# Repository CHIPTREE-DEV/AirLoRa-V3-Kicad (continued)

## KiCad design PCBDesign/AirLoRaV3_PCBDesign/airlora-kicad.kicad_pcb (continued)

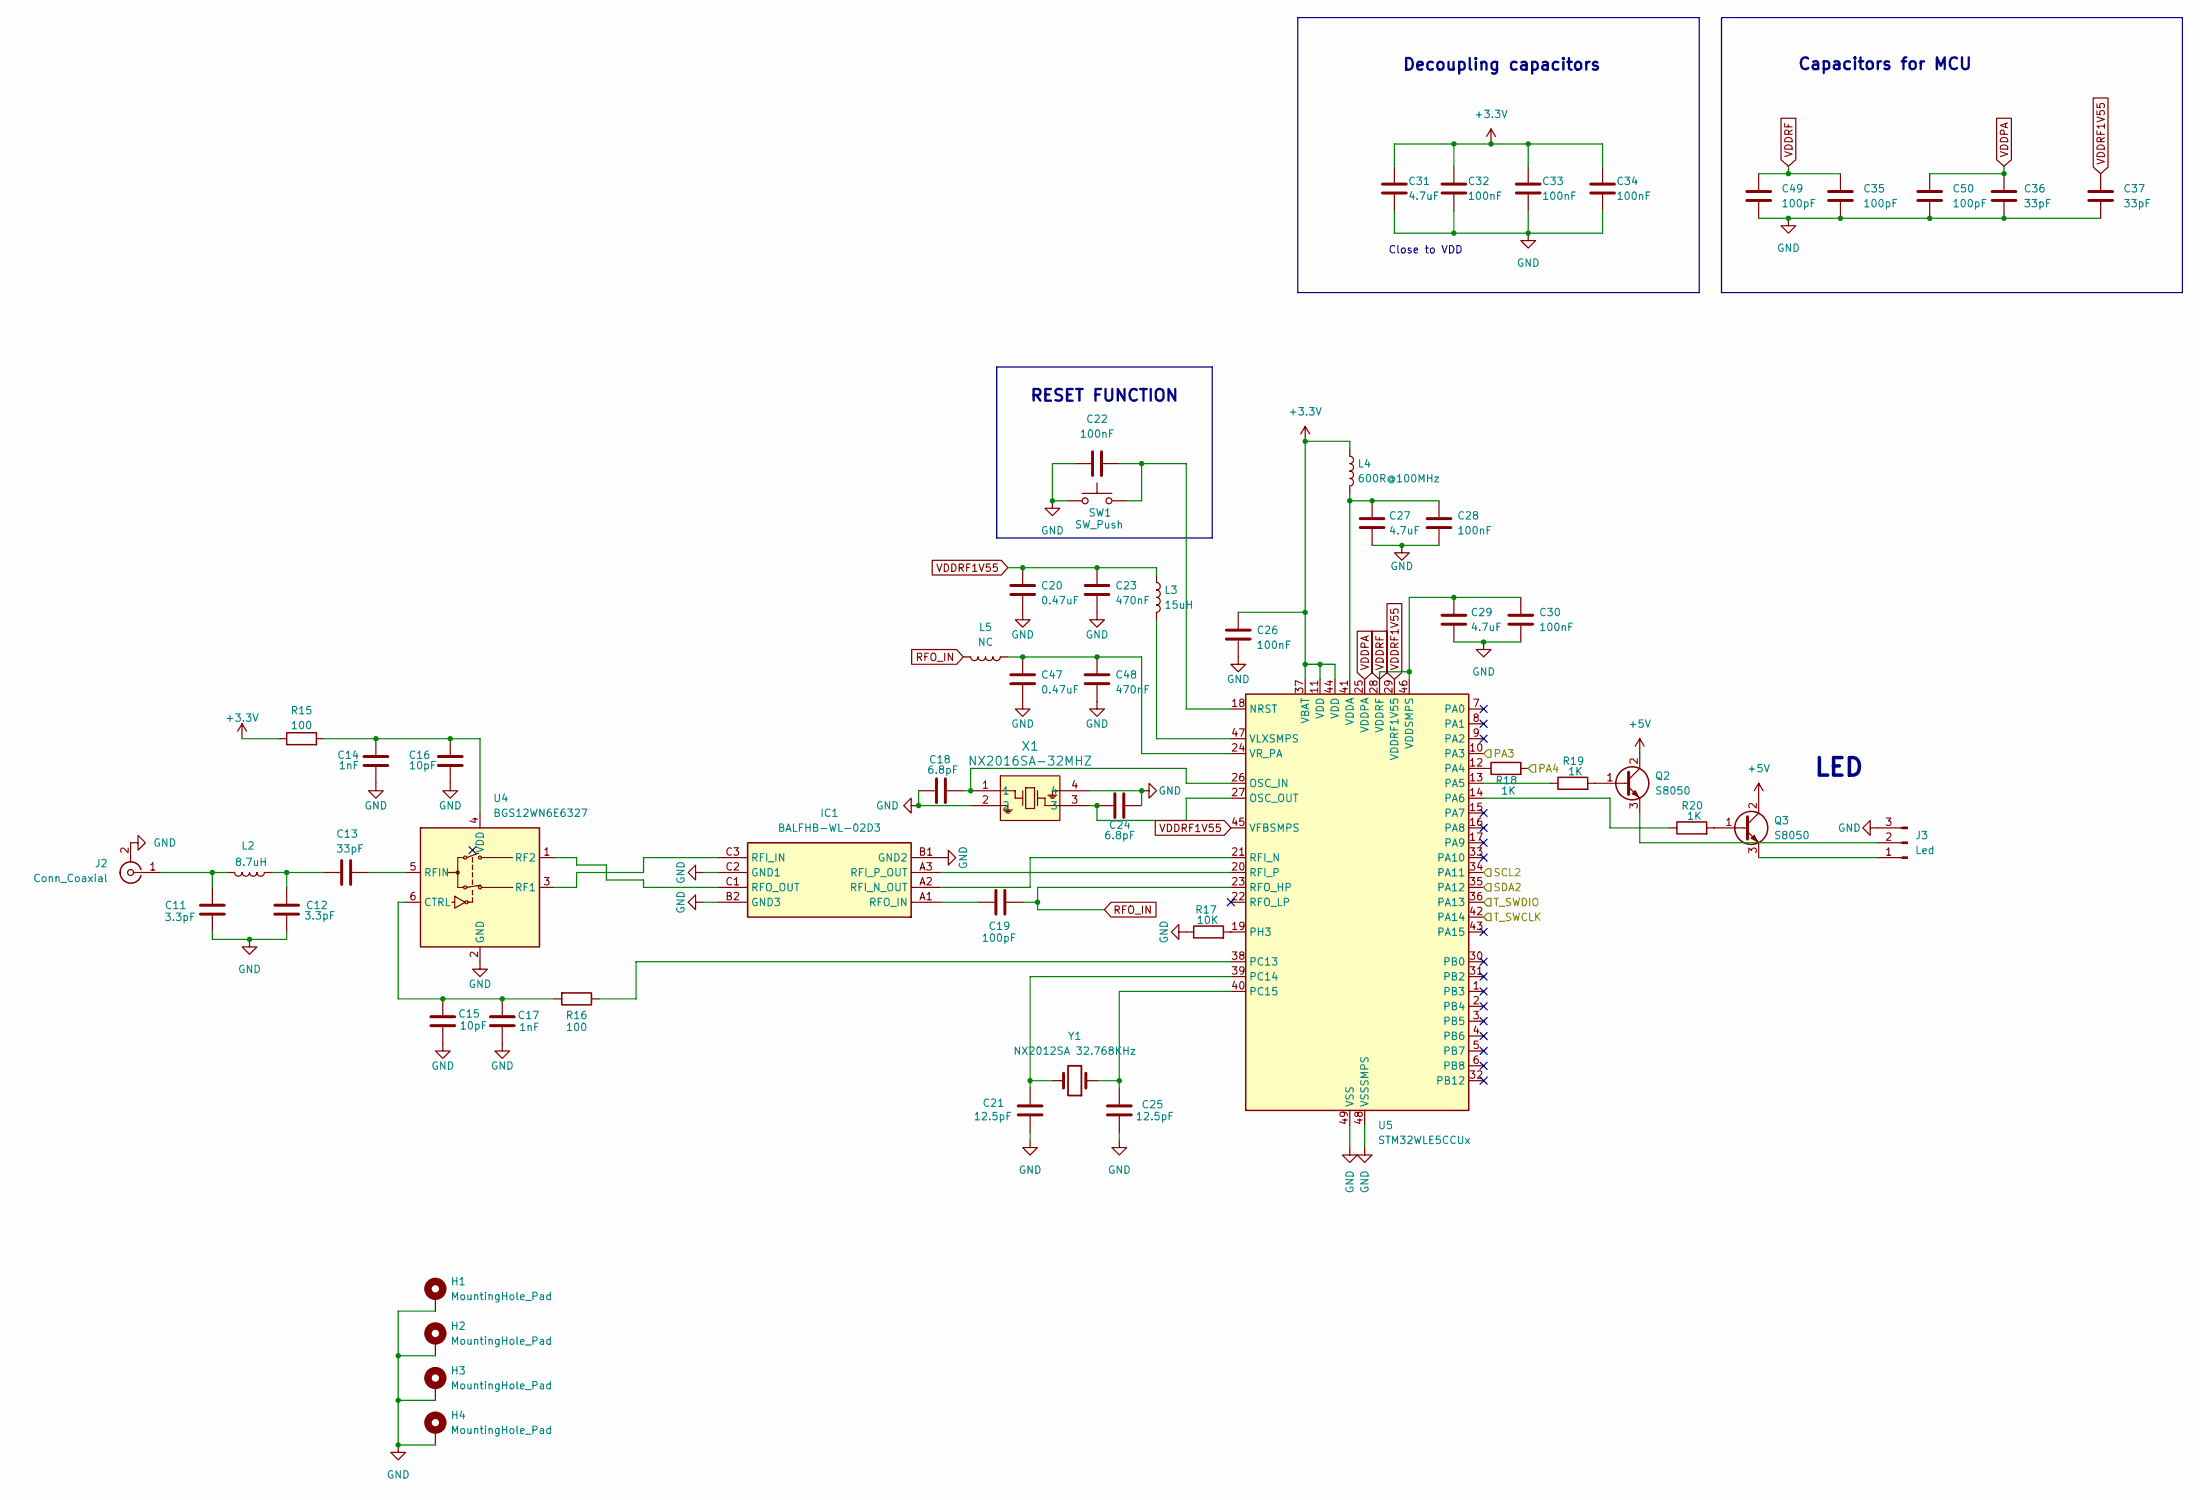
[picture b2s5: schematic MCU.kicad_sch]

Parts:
C11, C12: 3.3pF; C_0402_1005Metric_Pad0.74x0.62mm_HandSolder
C13, C36, C37: 33pF; C_0402_1005Metric_Pad0.74x0.62mm_HandSolder
C14, C17: 1nF; C_0402_1005Metric_Pad0.74x0.62mm_HandSolder
C15, C16: 10pF; C_0402_1005Metric_Pad0.74x0.62mm_HandSolder
C18, C24: 6.8pF; C_0402_1005Metric_Pad0.74x0.62mm_HandSolder
C19, C35, C49, C50: 100pF; C_0402_1005Metric_Pad0.74x0.62mm_HandSolder
C20, C47: 0.47uF; C_0402_1005Metric_Pad0.74x0.62mm_HandSolder
C21, C25: 12.5pF; C_0402_1005Metric_Pad0.74x0.62mm_HandSolder
C22, C26, C28, C30, C32, C33, C34: 100nF; C_0402_1005Metric_Pad0.74x0.62mm_HandSolder
C23, C48: 470nF; C_0402_1005Metric_Pad0.74x0.62mm_HandSolder
C27, C29, C31: 4.7uF; C_0402_1005Metric_Pad0.74x0.62mm_HandSolder
H1, H2, H3, H4: MountingHole_Pad; MountingHole_3mm_Pad_Via
IC1: BALFHB-WL-02D3; BALFHBWL05D3; Manufacturer_Part_Number BALFHB-WL-05D3; Mouser Part Number 511-BALFHB-WL-05D3
J2: Conn_Coaxial; U.FL_Molex_MCRF_73412-0110_Vertical
J3: Led; JST_XH_B3B-XH-A_1x03_P2.50mm_Vertical
L2: 8.7uH; L_0402_1005Metric_Pad0.77x0.64mm_HandSolder
L3: 15uH; L_0402_1005Metric_Pad0.77x0.64mm_HandSolder
L4: 600R@100MHz; L_0402_1005Metric_Pad0.77x0.64mm_HandSolder
L5: NC; L_0402_1005Metric_Pad0.77x0.64mm_HandSolder
Q2, Q3: S8050; SOT-23
R15, R16: 100; R_0402_1005Metric_Pad0.72x0.64mm_HandSolder
R17: 10K; R_0402_1005Metric_Pad0.72x0.64mm_HandSolder
R18, R19, R20: 1K; R_0402_1005Metric_Pad0.72x0.64mm_HandSolder
SW1: SW_Push; SW_Push_1P1T_NO_Vertical_Wuerth_434133025816
U4: BGS12WN6E6327; BGS12SN6E6327XTSA1
U5: STM32WLE5CCUx; QFN-48-1EP_7x7mm_P0.5mm_EP5.6x5.6mm
X1: NX2016SA-32MHZ; NX2016SA_NDK
Y1: NX2012SA 32.768KHz; XTAL_NX2012SA-32.768K-STD-MUB-1

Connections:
+3.3V: C26.1, C31.1, C32.1, C33.1, C34.1, L4.1, R15.1, U5.11 (VDD), U5.37 (VBAT), U5.44 (VDD); also elsewhere on the board
+5V: Q2.2 (C), Q3.2 (C); also elsewhere on the board
/AirLora V3/MCU Sub/PA8: R18.2; also elsewhere on the board
/AirLora V3/MCU Sub/SCL2: U5.34 (PA11); also elsewhere on the board
/AirLora V3/MCU Sub/SDA2: U5.35 (PA12); also elsewhere on the board
/AirLora V3/MCU/PA3: U5.10 (PA3); also elsewhere on the board
/AirLora V3/MCU/T_SWCLK: U5.42 (PA14); also elsewhere on the board
/AirLora V3/MCU/T_SWDIO: U5.36 (PA13); also elsewhere on the board
GND: C11.1, C12.1, C14.1, C15.2, C16.1, C17.2, C18.1, C20.2, C21.1, C22.1, C23.2, C24.2, C25.1, C26.2, C27.2, C28.2, C29.2, C30.2, C31.2, C32.2, C33.2, C34.2, C35.2, C36.2, C37.2, C47.2, C48.2, C49.2, C50.2, H1.1, H2.1, H3.1, H4.1, IC1.B1 (GND2), IC1.B2 (GND3), IC1.C2 (GND1), J2.2 (Ext), J3.3, R17.1, SW1.1, U4.2 (GND), U5.48 (VSSSMPS), U5.49 (VSS), X1.2, X1.4; also elsewhere on the board
unnamed: C12.2, C13.2, L2.1
unnamed: IC1.C3 (RFI_IN), U4.3 (RF1)
unnamed: IC1.A2 (RFI_N_OUT), U5.21 (RFI_N)
unnamed: IC1.A3 (RFI_P_OUT), U5.20 (RFI_P)
unnamed: C19.1, IC1.A1 (RFO_IN)
unnamed: IC1.C1 (RFO_OUT), U4.1 (RF2)
unnamed: C11.2, J2.1 (In), L2.2
unnamed: J3.1, Q3.3 (E)
unnamed: J3.2, Q2.3 (E)
unnamed: Q2.1 (B), R19.2
unnamed: Q3.1 (B), R20.2
unnamed: C15.1, C17.1, R16.2, U4.6 (CTRL)
unnamed: C13.1, U4.5 (RFIN)
unnamed: C14.2, C16.2, R15.2, U4.4 (VDD)
unnamed: C22.2, SW1.2, U5.18 (NRST)
unnamed: C18.2, U5.26 (OSC_IN), X1.1
unnamed: C24.1, U5.27 (OSC_OUT), X1.3
unnamed: R18.1, U5.12 (PA4)
unnamed: R19.1, U5.13 (PA5)
unnamed: R20.1, U5.14 (PA6)
unnamed: R16.1, U5.38 (PC13)
unnamed: C21.2, U5.39 (PC14), Y1.2
unnamed: C25.2, U5.40 (PC15), Y1.1
unnamed: R17.2, U5.19 (PH3)
unnamed: C27.1, C28.1, L4.2, U5.41 (VDDA)
unnamed: L3.2, U5.47 (VLXSMPS)
unnamed: C47.1, C48.1, L5.1, U5.24 (VR_PA)
RFO_IN: C19.2, L5.2, U5.23 (RFO_HP)
VDDPA: C36.1, C50.1, U5.25 (VDDPA)
VDDRF: C29.1, C30.1, C35.1, C49.1, U5.28 (VDDRF), U5.46 (VDDSMPS)
VDDRF1V55: C20.1, C23.1, C37.1, L3.1, U5.29 (VDDRF1V55), U5.45 (VFBSMPS)

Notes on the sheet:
Capacitors for MCU
RESET FUNCTION
Close to VDD
LED
Decoupling capacitors

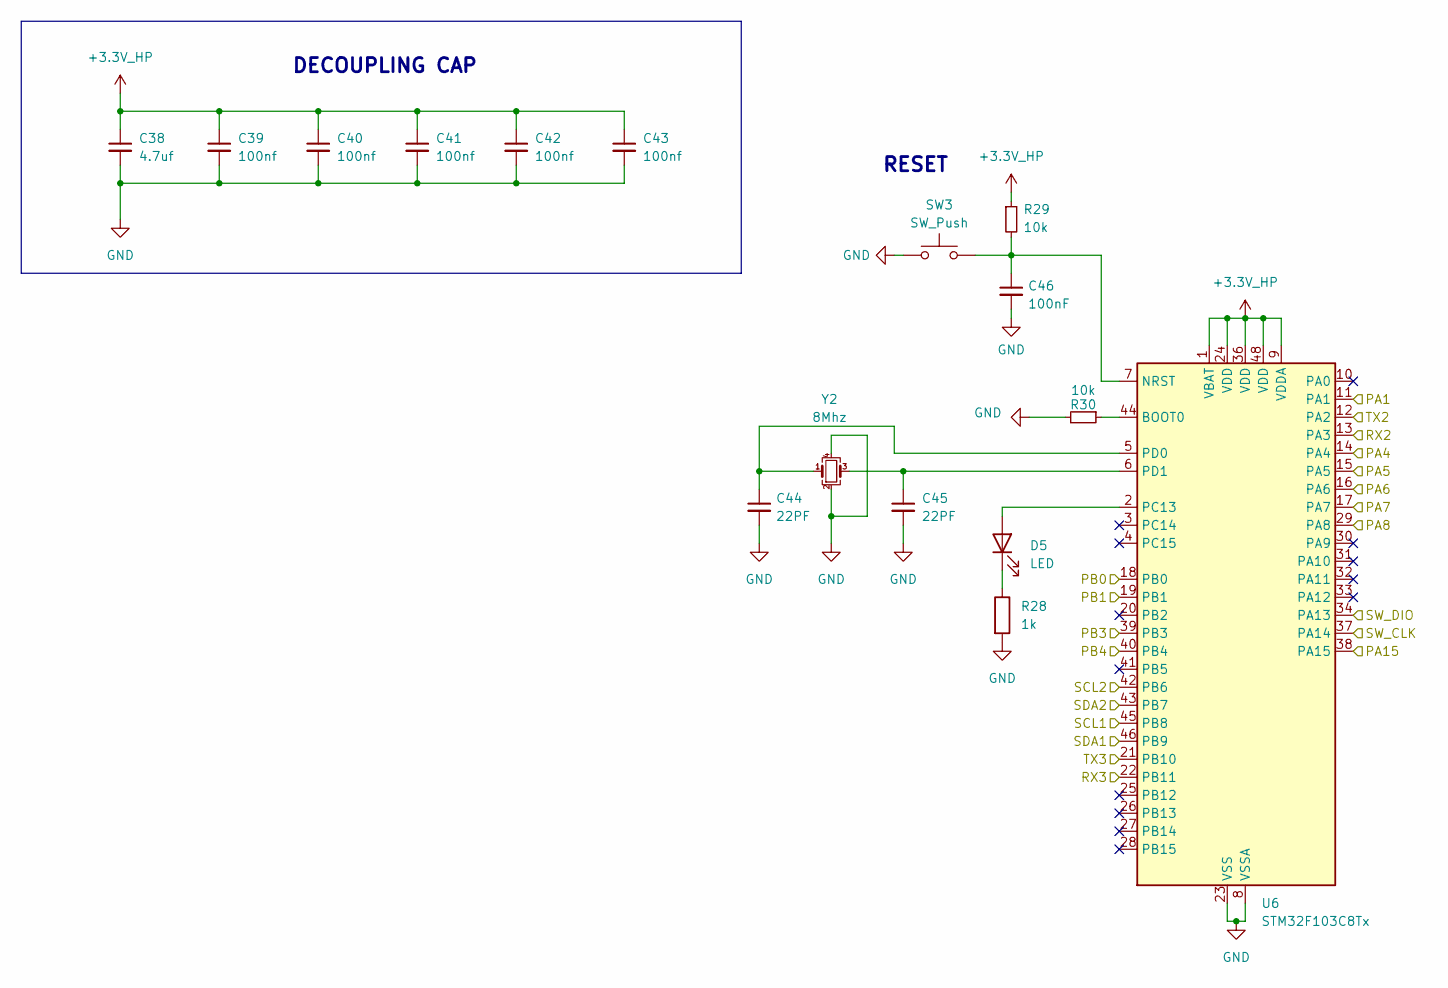
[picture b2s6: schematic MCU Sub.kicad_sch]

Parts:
C38: 4.7uf; C_0402_1005Metric_Pad0.74x0.62mm_HandSolder
C39, C40, C41, C42, C43: 100nf; C_0402_1005Metric_Pad0.74x0.62mm_HandSolder
C44, C45: 22PF; C_0402_1005Metric_Pad0.74x0.62mm_HandSolder
C46: 100nF; C_0402_1005Metric_Pad0.74x0.62mm_HandSolder
D5: LED; LED_0603_1608Metric_Pad1.05x0.95mm_HandSolder
R28: 1k; R_0402_1005Metric_Pad0.72x0.64mm_HandSolder
R29, R30: 10k; R_0402_1005Metric_Pad0.72x0.64mm_HandSolder
SW3: SW_Push; SW_Push_1P1T_NO_Vertical_Wuerth_434133025816
U6: STM32F103C8Tx; LQFP-48_7x7mm_P0.5mm
Y2: 8Mhz; Crystal_SMD_3225-4Pin_3.2x2.5mm

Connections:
+3.3V_HP: C38.1, C39.1, C40.1, C41.1, C42.1, C43.1, R29.1, U6.1 (VBAT), U6.9 (VDDA), U6.24 (VDD), U6.36 (VDD), U6.48 (VDD); also elsewhere on the board
/AirLora V3/MCU Sub/PA1: U6.11 (PA1)
/AirLora V3/MCU Sub/PA4: U6.14 (PA4); also elsewhere on the board
/AirLora V3/MCU Sub/PA5: U6.15 (PA5); also elsewhere on the board
/AirLora V3/MCU Sub/PA6: U6.16 (PA6); also elsewhere on the board
/AirLora V3/MCU Sub/PA7: U6.17 (PA7); also elsewhere on the board
/AirLora V3/MCU Sub/PA8: U6.29 (PA8); also elsewhere on the board
/AirLora V3/MCU Sub/PA15: U6.38 (PA15); also elsewhere on the board
/AirLora V3/MCU Sub/PB0: U6.18 (PB0); also elsewhere on the board
/AirLora V3/MCU Sub/PB1: U6.19 (PB1); also elsewhere on the board
/AirLora V3/MCU Sub/PB3: U6.39 (PB3); also elsewhere on the board
/AirLora V3/MCU Sub/PB4: U6.40 (PB4); also elsewhere on the board
/AirLora V3/MCU Sub/RX2: U6.13 (PA3)
/AirLora V3/MCU Sub/RX3: U6.22 (PB11); also elsewhere on the board
/AirLora V3/MCU Sub/SCL1: U6.45 (PB8); also elsewhere on the board
/AirLora V3/MCU Sub/SCL2: U6.42 (PB6); also elsewhere on the board
/AirLora V3/MCU Sub/SDA1: U6.46 (PB9); also elsewhere on the board
/AirLora V3/MCU Sub/SDA2: U6.43 (PB7); also elsewhere on the board
/AirLora V3/MCU Sub/SW_CLK: U6.37 (PA14); also elsewhere on the board
/AirLora V3/MCU Sub/SW_DIO: U6.34 (PA13); also elsewhere on the board
/AirLora V3/MCU Sub/TX2: U6.12 (PA2)
/AirLora V3/MCU Sub/TX3: U6.21 (PB10); also elsewhere on the board
GND: C38.2, C39.2, C40.2, C41.2, C42.2, C43.2, C44.2, C45.2, C46.2, R28.2, R30.2, SW3.1, U6.8 (VSSA), U6.23 (VSS), U6.35 (VSS), U6.47 (VSS), Y2.2, Y2.4; also elsewhere on the board
unnamed: D5.2 (A), U6.2 (PC13)
unnamed: D5.1 (K), R28.1
unnamed: R30.1, U6.44 (BOOT0)
unnamed: C46.1, R29.2, SW3.2, U6.7 (NRST)
unnamed: C44.1, U6.5 (PD0), Y2.1
unnamed: C45.1, U6.6 (PD1), Y2.3

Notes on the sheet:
RESET
DECOUPLING CAP

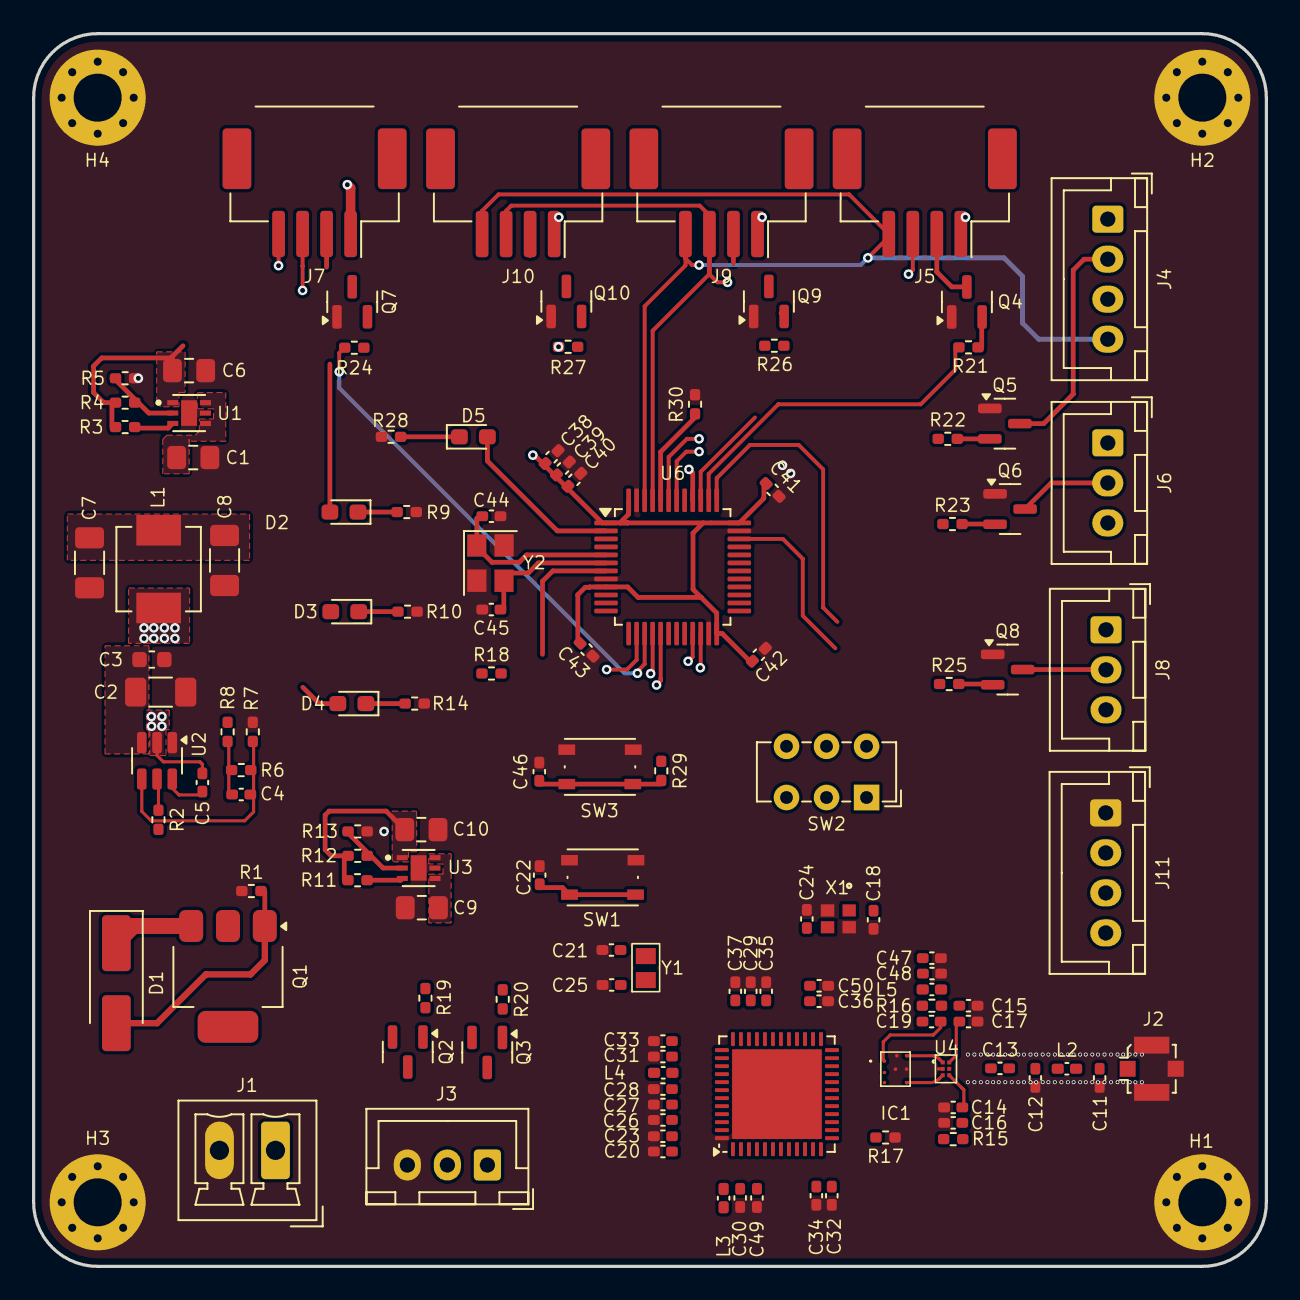
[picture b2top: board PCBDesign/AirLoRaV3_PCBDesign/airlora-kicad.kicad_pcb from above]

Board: 4 copper layers, 77.0 x 77.0 mm, 128 parts (0 on the bottom side), 93 nets.

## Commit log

2024-04-03 Just Testing
2024-04-03 testnewadmin
2024-04-03 TestAgain
2024-04-03 NewUpdate
2024-04-03 NewFolder
2024-04-03 NewFolderAdded
2024-04-03 PCBFolderAdded
2024-04-08 Updated Schematic
2024-04-25 Update circiut
2024-05-07 Update PCB layout
2024-05-15 Update schematic
2024-05-23 Update circuit buck converter and sensor
2024-05-29 Update PCB
2024-05-31 Update package and placement components
2024-06-01 Update Placement component
2024-06-05 refactored project
2024-06-05 removed polarity protection and fixed component placement
2024-06-06 Update layout PCB
2024-06-12 [Fix] Schematic and layout. - Replaced STM32WLE5x symbol for better visualization of the symbols - Added some missing connections - Modified some components' values - Changed the layout for STM32WL
2024-06-24 Update PCB layout and add Logo
2024-06-24 Update trace and vias for power
2024-06-25 Update power size track and add more vias
2024-06-25 [Fix] Adjust layout power trace
2024-07-06 Update inductor
2024-07-18 update problem
2024-07-24 Udpate test point
2024-07-25 Update schemtic
2024-08-01 Update antenna
2024-08-02 Update 3D model
2024-08-09 Update value resistor and transistor
